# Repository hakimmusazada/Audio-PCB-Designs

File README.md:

# Audio PCB Designs

Two analog audio boards designed in **KiCad 9**, from schematic to single-sided PCB to home fabrication with photoresist masks. The second project builds on the first.

| # | Project | Core IC | What it does | Status |
|---|---------|---------|--------------|--------|
| 01 | [Audio Amplifier](01-lm386-audio-amplifier/) | LM386 | Amplifies a line-level signal to drive a small speaker; on-board 9 V regulator and volume control | Hand-fabricated and tested during a university electronics course |
| 02 | [Audio Equalizer](02-tl072-audio-equalizer/) | TL072 | Active bass and treble tone control (Baxandall-style RC network) | Independent extension of project & Hand-fabricated as well 01 |

<p align="center">
  
  &nbsp;&nbsp;
  
</p>

## Repository layout

```
audio-pcb-designs/
├── 01-lm386-audio-amplifier/
│   ├── kicad/                  KiCad 9 project (.kicad_pro, .kicad_sch, .kicad_pcb)
│   ├── fabrication/
│   │   └── photoresist-masks/  Copper and silkscreen PDFs for UV exposure
│   ├── images/                 PCB layout and 3D render
│   └── lm386-audio-amplifier-bom.csv
└── 02-tl072-audio-equalizer/
    ├── kicad/
    ├── fabrication/
    │   ├── gerbers/            Gerber + drill files
    │   └── photoresist-masks/
    ├── images/                 Schematic, PCB layout and 3D render
    └── tl072-audio-equalizer-bom.csv
```

## Opening the designs

Install [KiCad](https://www.kicad.org/) 9.0 or newer and open the `.kicad_pro` file in either `kicad/` folder. Both projects use only KiCad's standard symbol and footprint libraries.

## Skills demonstrated

- Analog circuit design: power-amplifier gain setting, output stabilisation (Zobel network), op-amp biasing on a single supply, active RC tone-control filters
- Schematic capture, footprint selection and single-layer PCB routing in KiCad
- Design for home fabrication: wide tracks, large pads, mounting holes, printable photoresist masks
- Soldering, bring-up and bench testing

## Author

**Hakim Musazada**, Electrical and Electronics Engineering
[LinkedIn](https://www.linkedin.com/in/hakim-musazada/)

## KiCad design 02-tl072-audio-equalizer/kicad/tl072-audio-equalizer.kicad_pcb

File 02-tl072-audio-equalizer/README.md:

# 02 · Audio Equalizer (TL072)

An active **bass and treble tone control** built around the **TL072** dual op-amp. I designed it independently as an extension of the [LM386 amplifier](../01-lm386-audio-amplifier/): it sits in front of the power stage and lets the listener boost or cut low and high frequencies with two potentiometers.

<p align="center">
  
  &nbsp;
  
</p>

## How it works

The circuit runs from a single 9 V supply, so both op-amp inputs are referenced to a mid-rail bias of about 4.5 V.

1. **Bias (R1, R2, C1).** Two 100 kΩ resistors split the 9 V rail; C1 (1 µF) filters the midpoint, which feeds the non-inverting inputs of both op-amp halves.
2. **Input buffer (U1A).** C2 (2.2 µF) blocks DC from the source and R3 (100 kΩ) references the input. U1A is an inverting stage with R4 = R5 = 10 kΩ, giving unity gain and a low-impedance drive for the tone network.
3. **Tone network (U1B).** A Baxandall-style feedback network sits between the U1A output and the U1B output, with its centre taps going to the U1B inverting input:
   - **Treble (RV1, 100 kΩ):** R6/R7 (10 kΩ) on either side of the pot; C5 (1 nF) in series with the wiper only passes high frequencies, so RV1 shifts the high-frequency gain.
   - **Bass (RV2, 100 kΩ):** R8/R9 (22 kΩ) on either side of the pot, C6 (47 nF) across the pot and R10 (22 kΩ) from the wiper. At high frequencies C6 shorts the pot out, so RV2 only acts on low frequencies.
   - With both pots centred the response is flat; turning a pot one way boosts its band, the other way cuts it.
4. **Output (C7, R11).** C7 (10 µF) removes the 4.5 V DC level and R11 (47 kΩ) references the output to ground.
5. **Supply decoupling.** C3 (100 nF) and C4 (100 µF) at the op-amp supply pin.

## PCB

| Property | Value |
|----------|-------|
| Layers | Single-sided (bottom copper) |
| Board size | 58.5 × 61.5 mm |
| Track width | 1.0 mm |
| Op-amp | DIP-8 in a socket |
| Controls | 2 × board-mounted 100 kΩ potentiometers |
| Fabrication | Photoresist masks in [`fabrication/photoresist-masks/`](fabrication/photoresist-masks/); Gerber and drill files in [`fabrication/gerbers/`](fabrication/gerbers/) |

## Bill of materials

| Ref | Qty | Value | Role |
|-----|-----|-------|------|
| U1 | 1 | TL072 | Dual op-amp (DIP-8) |
| R1, R2, R3 | 3 | 100 kΩ | Bias divider, input reference |
| R4, R5, R6, R7 | 4 | 10 kΩ | Buffer gain, treble network |
| R8, R9, R10 | 3 | 22 kΩ | Bass network |
| R11 | 1 | 47 kΩ | Output reference |
| RV1 | 1 | 100 kΩ pot | Treble |
| RV2 | 1 | 100 kΩ pot | Bass |
| C1 | 1 | 1 µF 35 V | Bias filter |
| C2 | 1 | 2.2 µF 25 V | Input coupling |
| C3 | 1 | 100 nF | Supply decoupling |
| C4 | 1 | 100 µF 35 V | Supply bulk |
| C5 | 1 | 1 nF | Treble network |
| C6 | 1 | 47 nF | Bass network |
| C7 | 1 | 10 µF 25 V | Output coupling |
| IN, OUT, PWR | 3 | 2-pin header | Connectors |

Also available as [`tl072-audio-equalizer-bom.csv`](tl072-audio-equalizer-bom.csv).

## Files

- [`kicad/`](kicad/): open `tl072-audio-equalizer.kicad_pro` in KiCad 9+
- [`fabrication/gerbers/`](fabrication/gerbers/): copper, silkscreen, board outline and drill files
- [`fabrication/photoresist-masks/`](fabrication/photoresist-masks/): copper and silkscreen PDFs for UV exposure

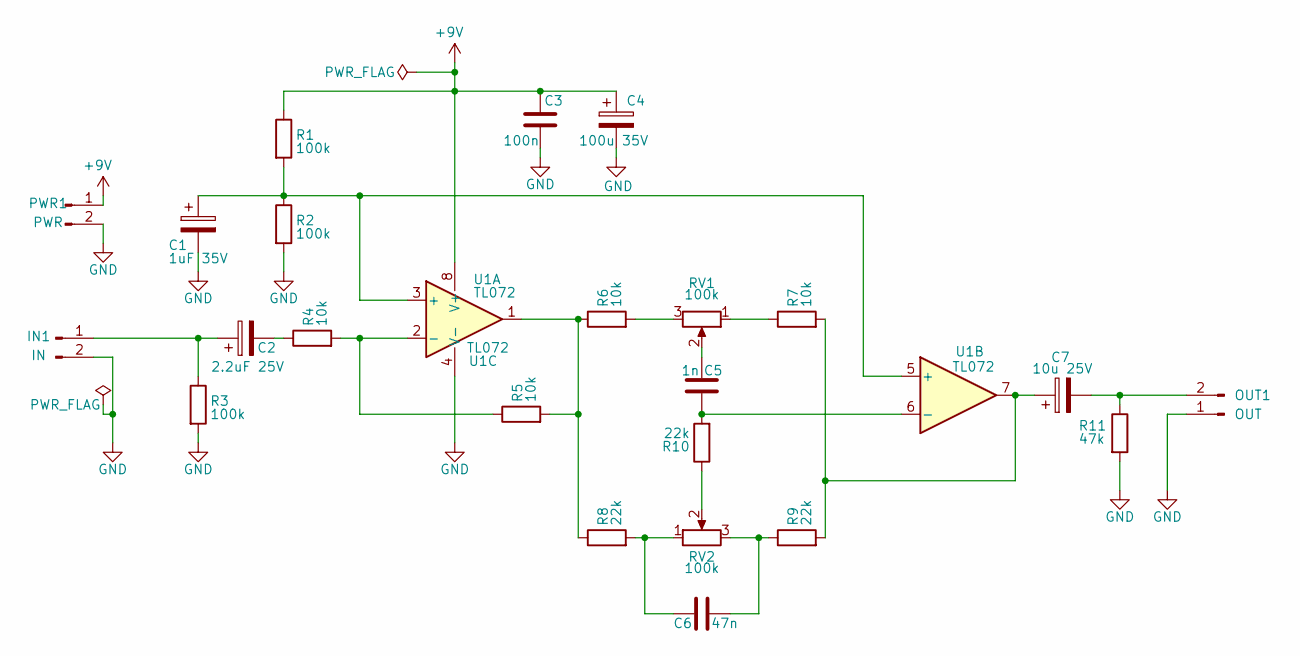
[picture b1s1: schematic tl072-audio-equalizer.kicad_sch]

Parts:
C1: 1uF 35V; CP_Radial_D5.0mm_P2.50mm
C2: 2.2uF 25V; CP_Radial_D5.0mm_P2.00mm
C3: 100n; C_Disc_D5.1mm_W3.2mm_P5.00mm
C4: 100u 35V; CP_Radial_D8.0mm_P3.80mm
C5: 1n; C_Rect_L7.0mm_W3.5mm_P5.00mm
C6: 47n; C_Rect_L10.0mm_W4.0mm_P7.50mm_FKS3_FKP3
C7: 10u 25V; CP_Radial_D5.0mm_P2.00mm
IN1: IN; PinHeader_1x02_P2.54mm_Vertical
OUT1: OUT; PinHeader_1x02_P2.54mm_Vertical
PWR1: PWR; PinHeader_1x02_P2.54mm_Vertical
R1, R2, R3: 100k; R_Axial_DIN0207_L6.3mm_D2.5mm_P10.16mm_Horizontal
R4, R5, R6, R7: 10k; R_Axial_DIN0207_L6.3mm_D2.5mm_P10.16mm_Horizontal
R8, R9, R10: 22k; R_Axial_DIN0207_L6.3mm_D2.5mm_P10.16mm_Horizontal
R11: 47k; R_Axial_DIN0207_L6.3mm_D2.5mm_P10.16mm_Horizontal
RV1, RV2: 100k; Potentiometer_Alps_RK163_Single_Horizontal
U1: TL072; DIP-8_W7.62mm_Socket_LongPads

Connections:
+9V: C3.1, C4.1, PWR1.1, R1.1, U1.8 (V+)
GND: C1.2, C3.2, C4.2, IN1.2, OUT1.1, PWR1.2, R2.2, R3.2, R11.2, U1.4 (V-)
unnamed: C2.2, R4.1
unnamed: C5.1, RV1.2
unnamed: C6.1, R8.2, RV2.1
unnamed: C6.2, R9.1, RV2.3
unnamed: C7.1, R7.2, R9.2, U1.7
unnamed: C2.1, IN1.1, R3.1
unnamed: C7.2, OUT1.2, R11.1
unnamed: R5.2, R6.1, R8.1, U1.1
unnamed: R6.2, RV1.3
unnamed: R7.1, RV1.1
unnamed: R10.1, RV2.2
unnamed: C1.1, R1.2, R2.1, U1.3 (+), U1.5 (+)
unnamed: R4.2, R5.1, U1.2 (-)
unnamed: C5.2, R10.2, U1.6 (-)

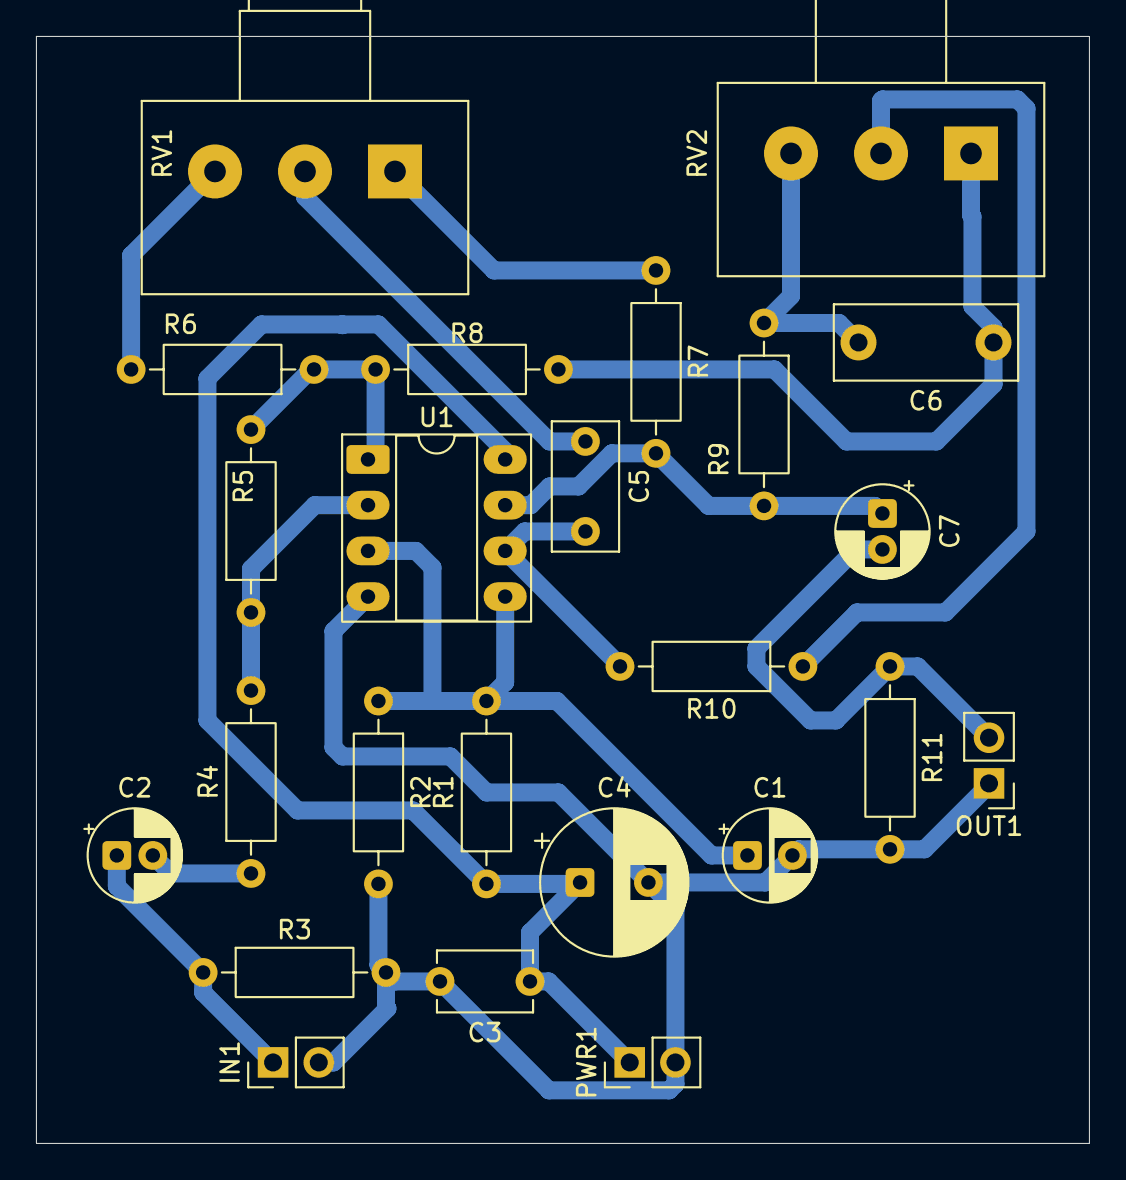
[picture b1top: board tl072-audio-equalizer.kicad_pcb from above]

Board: 2 copper layers, 58.5 x 61.5 mm, 24 parts (0 on the bottom side), 16 nets.

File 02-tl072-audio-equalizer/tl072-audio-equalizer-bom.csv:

Reference,Qty,Value,Description
U1,1,TL072,Dual JFET-input op-amp (DIP-8)
R1 R2 R3,3,100k,Resistor (bias divider / input reference)
R4 R5 R6 R7,4,10k,Resistor
R8 R9 R10,3,22k,Resistor
R11,1,47k,Resistor (output reference)
RV1,1,100k,Potentiometer - treble
RV2,1,100k,Potentiometer - bass
C1,1,1uF 35V,Electrolytic (bias filter)
C2,1,2.2uF 25V,Electrolytic (input coupling)
C3,1,100nF,Ceramic (supply decoupling)
C4,1,100uF 35V,Electrolytic (supply bulk)
C5,1,1nF,Film/ceramic (treble network)
C6,1,47nF,Film (bass network)
C7,1,10uF 25V,Electrolytic (output coupling)
IN OUT PWR,3,Conn_01x02,2-pin header

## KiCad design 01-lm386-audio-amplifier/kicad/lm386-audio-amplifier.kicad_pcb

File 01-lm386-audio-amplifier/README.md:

# 01 · Audio Amplifier (LM386)

A compact single-sided audio power amplifier built around the **LM386**. It takes a line-level signal (phone, MP3 player, signal generator), adds a volume control, and drives a small 8 Ω speaker. The board was hand-fabricated and tested during a university electronics course.

<p align="center">
  
  &nbsp;
  
</p>

## Circuit overview

| Block | Parts | Function |
|-------|-------|----------|
| Power input | J1, C6 (100 µF), C5 (100 nF) | DC input with bulk and high-frequency filtering |
| Regulator | U2 L7809, C2 (470 µF), C1 (100 nF) | Regulated 9 V rail for the amplifier |
| Volume | J2 (IN), RV1 10 kΩ | Input signal goes to the top of the pot; the wiper feeds the LM386 non-inverting input |
| Amplifier | U1 LM386, C3 (10 µF across pins 1–8) | Capacitor between the gain pins raises the voltage gain from 20 to about 200 (≈46 dB) |
| Output | C7 (250 µF), J3 (OUT) | DC-blocking capacitor to the speaker |
| Stability | R1 (10 Ω) + C4 (50 nF) | Zobel network on the output to prevent high-frequency oscillation |

The input of the 7809 needs a couple of volts of headroom, so the board should be fed from roughly 12 V DC.

## PCB

| Property | Value |
|----------|-------|
| Layers | 1 (bottom copper) |
| Board size | 39.5 × 49.5 mm |
| Track width | 1.2 mm |
| Mounting | 4 × corner holes |
| Fabrication | Photoresist (UV exposure) using the PDF masks in [`fabrication/photoresist-masks/`](fabrication/photoresist-masks/) |

## Bill of materials

| Ref | Qty | Value |
|-----|-----|-------|
| U1 | 1 | LM386 (DIP-8) |
| U2 | 1 | L7809 (TO-220) |
| RV1 | 1 | 10 kΩ potentiometer |
| R1 | 1 | 10 Ω |
| C1, C5 | 2 | 100 nF |
| C2 | 1 | 470 µF 16 V |
| C3 | 1 | 10 µF 16 V |
| C4 | 1 | 50 nF |
| C6 | 1 | 100 µF 25 V |
| C7 | 1 | 250 µF 16 V |
| J1, J2, J3 | 3 | 2-pin header (PWR, IN, OUT) |

Also available as [`lm386-audio-amplifier-bom.csv`](lm386-audio-amplifier-bom.csv).

## Files

- [`kicad/`](kicad/): open `lm386-audio-amplifier.kicad_pro` in KiCad 9+
- [`fabrication/photoresist-masks/`](fabrication/photoresist-masks/): copper and silkscreen layers as PDFs

## Next step

This board became the starting point for [project 02, the TL072 audio equalizer](../02-tl072-audio-equalizer/), which adds bass and treble control in front of the amplifier stage.

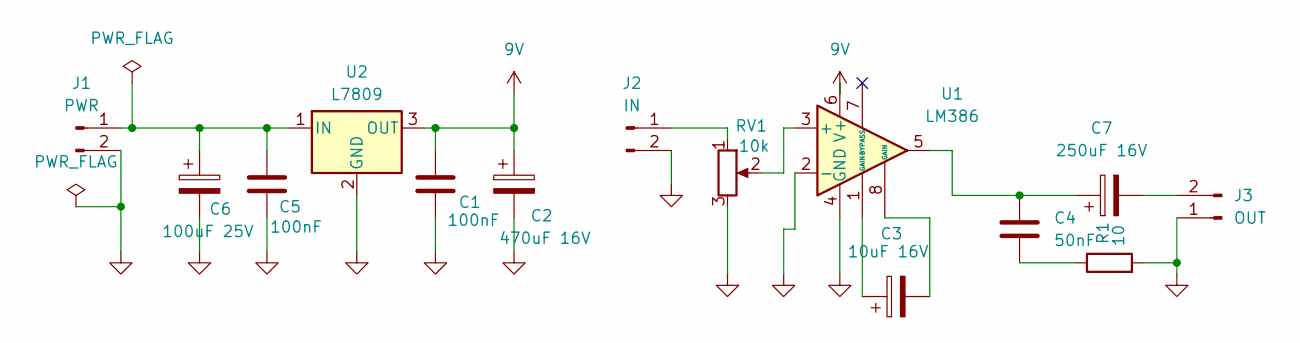
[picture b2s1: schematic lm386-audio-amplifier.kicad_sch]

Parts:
C1, C5: 100nF; C_Disc_D5.1mm_W3.2mm_P5.00mm
C2: 470uF 16V; CP_Radial_D8.0mm_P3.50mm
C3: 10uF 16V; CP_Radial_D5.0mm_P2.50mm
C4: 50nF; C_Disc_D5.1mm_W3.2mm_P5.00mm
C6: 100uF 25V; CP_Radial_D6.3mm_P2.50mm
C7: 250uF 16V; CP_Radial_D8.0mm_P3.50mm
J1: PWR; PinHeader_1x02_P2.54mm_Vertical
J2: IN; PinHeader_1x02_P2.54mm_Vertical
J3: OUT; PinHeader_1x02_P2.54mm_Vertical
R1: 10; R_Axial_DIN0207_L6.3mm_D2.5mm_P10.16mm_Horizontal
RV1: 10k; Potentiometer_Alps_RK163_Single_Horizontal
U1: LM386; DIP-8_W7.62mm_LongPads
U2: L7809; TO-220-3_Vertical

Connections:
9V: C1.1, C2.1, U1.6 (V+), U2.3 (OUT)
unnamed: C3.1, U1.1 (GAIN)
unnamed: C3.2, U1.8 (GAIN)
unnamed: C4.1, C7.1, U1.5
unnamed: C4.2, R1.1
unnamed: C5.1, C6.1, J1.1, U2.1 (IN)
unnamed: J2.1, RV1.1
unnamed: C7.2, J3.2
unnamed: RV1.2, U1.3 (+)
~: C1.2, C2.2, C5.2, C6.2, J1.2, J2.2, J3.1, R1.2, RV1.3, U1.2 (-), U1.4 (GND), U2.2 (GND)

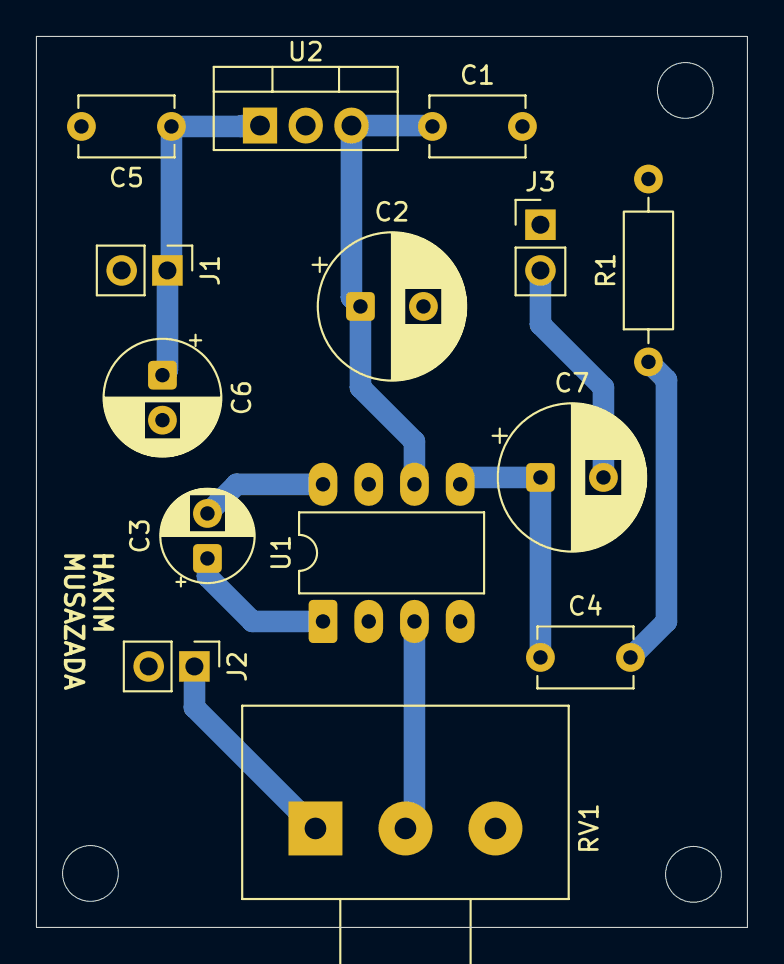
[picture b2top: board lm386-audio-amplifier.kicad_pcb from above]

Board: 2 copper layers, 39.5 x 49.5 mm, 14 parts (0 on the bottom side), 10 nets.

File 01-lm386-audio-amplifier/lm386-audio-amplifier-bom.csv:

"Reference","Qty","Value"
"C1,C5","2","100nF"
"C2","1","470uF 16V"
"C3","1","10uF 16V"
"C4","1","50nF"
"C6","1","100uF 25V"
"C7","1","250uF 16V"
"J1","1","PWR"
"J2","1","IN"
"J3","1","OUT"
"R1","1","10"
"RV1","1","10k"
"U1","1","LM386"
"U2","1","L7809"
